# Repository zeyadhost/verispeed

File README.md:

# Verispeed

A MIDI controller with 12 keys, 2 knobs and a screen. It works with music programs on a laptop.

Verispeed is one circuit board (PCB). It has no case. The 12 keys have the layout of one piano octave: 7 white keys and 5 black keys. The screen is in the center. There is one knob on each side of the screen.

The board has no speaker, so it does not make sound. It is a MIDI device. Connect it to a laptop with a USB-C cable. A music program on the laptop makes the sound. The program can be a DAW (digital audio workstation) or a software synthesizer.

The board also has Bluetooth LE. You can use it with a phone or a tablet.

Status: The design is finished and has no errors. The board is not built yet. The firmware is not written yet.

## Features

- 12 keys (MX-style switches), with 1 diode for each key
- 2 rotary encoders with a push button
- 2 inch color screen, 240 x 320 pixels
- ESP32-S3 module with USB and Bluetooth LE (8 MB flash, 2 MB PSRAM)
- Power from USB-C or from a 1-cell LiPo battery
- Battery charger on the board (200 mA)
- BOOT button, RESET button, serial header and 5 test points
- Board size 155 mm x 99 mm, 2 layers, 4 holes for M3 screws

## How it works

- Power: USB-C gives 5 V. A diode (D1) sends the 5 V to the system rail (SYS). The regulator U4 makes 3.3 V from SYS.
- Power source: When USB is connected, the P-MOSFET Q1 disconnects the battery. When USB is not connected, Q1 connects the battery.
- Battery: The charger U3 charges the battery at 200 mA. The red LED D2 is on while the battery charges. The slide switch SW4 disconnects the battery from the board. The charger still works when SW4 is off.
- Battery level: R6 and R7 divide the battery voltage by 2. GPIO1 reads the result. Multiply the value by 2 to get the battery voltage.
- USB: U2 protects the USB data lines from static electricity. R1 and R2 tell a USB-C power source to give 5 V. The ESP32-S3 has native USB, so it can be a USB-MIDI device with no extra chip.
- Keys: The 12 keys are in a matrix of 3 rows and 4 columns. The diode of each key points from the column to the row.
- Screen: The screen connects to the header J4 and uses the default SPI pins. GPIO14 controls the backlight.
- Firmware: To load new firmware, hold the BOOT button (SW2) and push the RESET button (SW1). The ESP32-S3 then waits for new firmware on USB. The header J3 has GND, TX and RX for a serial adapter.
- Test points: TP1 is 5 V from USB. TP2 is the battery. TP3 is SYS. TP4 is 3.3 V. TP5 is GND.

## Pictures

The picture shows the wires of the PCB. Red wires are on the top side. Blue wires are on the bottom side. The picture does not show the ground fill.

The flag and the signature are on the silkscreen (the white print on the board). Their SVG files are in [pcb-v2/silkscreen-art](pcb-v2/silkscreen-art/).

## Parts

The full build costs about $75. The prices are from 2 November 2026 and do not include shipping. Check the stock and the part numbers again before you order.

The LCSC parts cost about $24, the screen about $11, the battery about $10 and the PCB about $12. The switches, keycaps, knobs and screws cost the rest.

| Qty | Part | Reference | Where to buy |
|---|---|---|---|
| 1 | ESP32-S3-WROOM-1-N8R2 module | U5 | LCSC C2913204 |
| 1 | MCP73831-2-OT battery charger | U3 | LCSC C14879 |
| 1 | AP2112K-3.3 regulator | U4 | LCSC C51118 |
| 1 | USBLC6-2SC6 USB protection | U2 | LCSC C7519 |
| 1 | AO3401A P-MOSFET | Q1 | LCSC C15127 |
| 12 | 1N4148W diode | D3 to D14 | LCSC C81598 |
| 1 | SS14 Schottky diode | D1 | LCSC C2480 |
| 1 | KT-0603R red LED | D2 | LCSC C2286 |
| 1 | GCT USB4085 USB-C socket | J1 | LCSC C7095263 |
| 1 | JST B2B-PH-K-S battery socket | J2 | LCSC C131337 |
| 1 | 1 x 3 pin header, 2.54 mm | J3 | LCSC C49257 |
| 1 | 1 x 8 pin header, 2.54 mm, long pins | J4 | LCSC C492407 |
| 2 | Omron B3F-1000 push button | SW1 (RESET), SW2 (BOOT) | LCSC C93157 |
| 1 | G-Switch SK-12D02-G050 slide switch | SW4 | LCSC C5211273 |
| 2 | Alps EC11E15244G1 rotary encoder | ENC1, ENC2 | LCSC C370970 |
| 2 | 100 nF capacitor, 0603 | C5, C6 | LCSC C1591 |
| 2 | 1 uF capacitor, 0603 | C3, C7 | LCSC C15849 |
| 2 | 4.7 uF capacitor, 0805 | C1, C2 | LCSC C1779 |
| 1 | 10 uF capacitor, 0805 | C4 | LCSC C15850 |
| 1 | 1 kOhm resistor, 0603 | R5 | LCSC C21190 |
| 1 | 4.99 kOhm resistor, 0603 (the schematic says 5 kOhm) | R4 | LCSC C23046 |
| 2 | 5.1 kOhm resistor, 0603 | R1, R2 | LCSC C23186 |
| 2 | 10 kOhm resistor, 0603 | R8, R9 | LCSC C25804 |
| 3 | 100 kOhm resistor, 0603 | R3, R6, R7 | LCSC C25803 |
| 1 | Waveshare 2 inch LCD module (SKU 17344) | J4 | Waveshare |
| 1 | LiPo battery, 3.7 V, 1200 mAh, JST-PH plug (Adafruit 258) | J2 | Adafruit |
| 12 | MX-style switch, 5 pin, PCB mount | K1 to K12 | Keyboard shop |
| 12 | Keycap, 1u | K1 to K12 | Keyboard shop |
| 2 | Knob for a 6 mm flat (D-cut) shaft | ENC1, ENC2 | Any shop |
| 4 | M3 standoff, female-female, 12 mm or longer | H1 to H4 | Any shop |
| 4 | M3 x 6 screw | H1 to H4 | Any shop |
| 4 | M2 x 6 stud and screw for the screen | J4 | Any shop |

Warning: On J2, pin 1 is plus and pin 2 is minus. Some batteries have the wires in the opposite order. Use a multimeter to check the plug before you connect the battery.

## Pin map

| Function | ESP32-S3 GPIO |
|---|---|
| Key rows ROW1, ROW2, ROW3 | 4, 5, 6 |
| Key columns COL1, COL2, COL3, COL4 | 7, 15, 16, 17 |
| Encoder 1: A, B, button | 18, 21, 38 |
| Encoder 2: A, B, button | 47, 48, 2 |
| Screen: MOSI, SCK, CS, DC, RST, backlight | 11, 12, 10, 9, 8, 14 |
| Battery level (half of the battery voltage) | 1 |
| USB D-, D+ | 19, 20 |
| Serial header J3: TX, RX | 43, 44 |
| BOOT button | 0 |
| RESET button | EN |

## Key matrix

Each key connects a column to a diode. The diode connects to the row.

| Key | Row | Column | Position |
|---|---|---|---|
| K1 | ROW1 | COL1 | 1st white key (left) |
| K5 | ROW2 | COL1 | 2nd white key |
| K2 | ROW1 | COL2 | 3rd white key |
| K6 | ROW2 | COL2 | 4th white key |
| K3 | ROW1 | COL3 | 5th white key |
| K7 | ROW2 | COL3 | 6th white key |
| K4 | ROW1 | COL4 | 7th white key (right) |
| K9 | ROW3 | COL1 | 1st black key (left) |
| K10 | ROW3 | COL2 | 2nd black key |
| K11 | ROW3 | COL3 | 3rd black key |
| K12 | ROW3 | COL4 | 4th black key |
| K8 | ROW2 | COL4 | 5th black key (right) |

## Open the design

Open `pcb-v2/audio.kicad_pro` in KiCad 10. Keep the files and folders of `pcb-v2` together.

To run the checks from the command line:

```bash
cd pcb-v2
kicad-cli sch erc audio.kicad_sch
kicad-cli pcb drc --refill-zones --schematic-parity audio.kicad_pcb
```

ERC shows 0 violations. DRC shows 0 errors, 0 unconnected items and 0 differences from the schematic. DRC also shows 21 warnings. All 21 warnings are about the silkscreen.

## Files

```
pcb-v2/
  audio.kicad_pro       project file (open this file)
  audio.kicad_sch       schematic
  audio.kicad_pcb       PCB layout
  fp-lib-table          list of footprint libraries
  verispeed-v2.pretty/  custom footprints
  3dmodels/             3D models of the encoder and the screen
  silkscreen-art/       SVG files of the flag and the signature
images/                 pictures for this page and the journal
JOURNAL.md              development log
```

## Credits

- The Hack Club flag is from [assets.hackclub.com](https://assets.hackclub.com/).
- The 3D models of the Alps encoder and the Waveshare screen are from the makers. The other 3D models are from the KiCad library.

## License

MIT License. See [LICENSE](LICENSE).

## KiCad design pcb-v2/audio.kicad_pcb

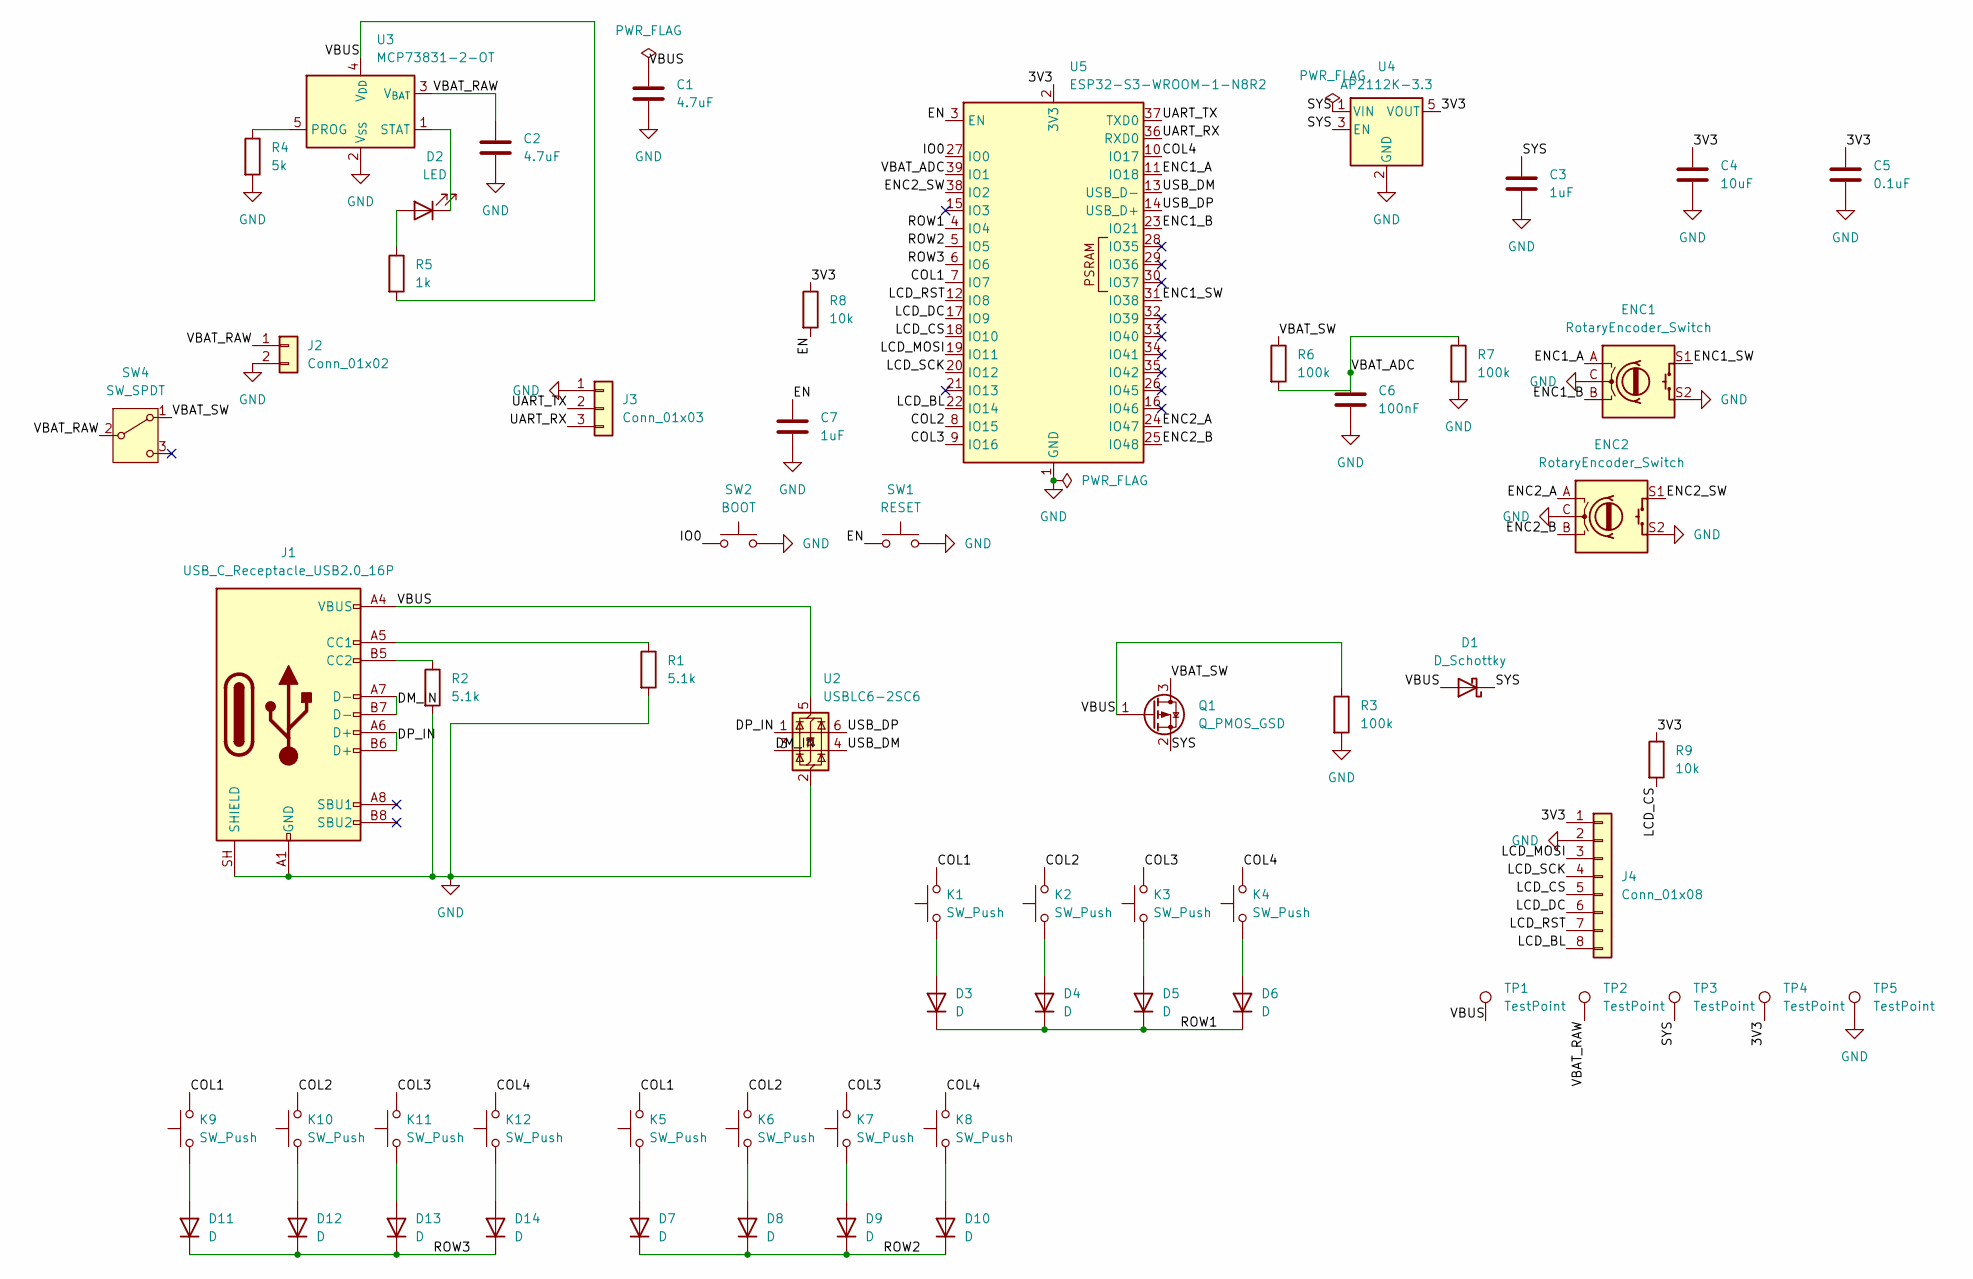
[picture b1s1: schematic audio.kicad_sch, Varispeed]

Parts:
C1, C2: 4.7uF; C_0805_2012Metric_Pad1.18x1.45mm_HandSolder
C3, C7: 1uF; C_0603_1608Metric_Pad1.08x0.95mm_HandSolder
C4: 10uF; C_0805_2012Metric_Pad1.18x1.45mm_HandSolder
C5: 0.1uF; C_0603_1608Metric_Pad1.08x0.95mm_HandSolder
C6: 100nF; C_0603_1608Metric_Pad1.08x0.95mm_HandSolder
D1: D_Schottky; D_SMA
D2: LED; LED_0603_1608Metric_Pad1.05x0.95mm_HandSolder
D3, D4, D5, D6, D7, D8, D9, D10, D11, D12, D13, D14: D; D_SOD-123
ENC1, ENC2: RotaryEncoder_Switch; RotaryEncoder_Alps_EC11E15244G1_Vertical
J1: USB_C_Receptacle_USB2.0_16P; USB_C_Receptacle_GCT_USB4085_FinePitch
J2: Conn_01x02; JST_PH_B2B-PH-K_1x02_P2.00mm_Vertical
J3: Conn_01x03; PinHeader_1x03_P2.54mm_Vertical
J4: Conn_01x08; Waveshare_2inch_LCD_Module
K1, K2, K3, K4, K5, K6, K7, K8, K9, K10, K11, K12: SW_Push; SW_Cherry_MX_1.00u_PCB
Q1: Q_PMOS_GSD; SOT-23
R1, R2: 5.1k; R_0603_1608Metric_Pad0.98x0.95mm_HandSolder
R3, R6, R7: 100k; R_0603_1608Metric_Pad0.98x0.95mm_HandSolder
R4: 5k; R_0603_1608Metric_Pad0.98x0.95mm_HandSolder
R5: 1k; R_0603_1608Metric_Pad0.98x0.95mm_HandSolder
R8, R9: 10k; R_0603_1608Metric_Pad0.98x0.95mm_HandSolder
SW1: RESET; SW_TH_Tactile_Omron_B3F-100x
SW2: BOOT; SW_TH_Tactile_Omron_B3F-100x
SW4: SW_SPDT; SW_Slide_SPDT_Angled_GSwitch_SK-12D02
TP1, TP2, TP3, TP4, TP5: TestPoint; TestPoint_Pad_D2.0mm
U2: USBLC6-2SC6; SOT-23-6
U3: MCP73831-2-OT; SOT-23-5
U4: AP2112K-3.3; SOT-23-5
U5: ESP32-S3-WROOM-1-N8R2; ESP32-S3-WROOM-1_Via0.3mm

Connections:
/3V3: C4.1, C5.1, J4.1, R8.1, R9.1, TP4.1 (1_1), U4.5 (VOUT), U5.2 (3V3)
/COL1: K1.2, K5.2, K9.2, U5.7 (IO7)
/COL2: K2.2, K6.2, K10.2, U5.8 (IO15)
/COL3: K3.2, K7.2, K11.2, U5.9 (IO16)
/COL4: K4.2, K8.2, K12.2, U5.10 (IO17)
/DM_IN: J1.A7 (D-), J1.B7 (D-), U2.3 (I/O2)
/DP_IN: J1.A6 (D+), J1.B6 (D+), U2.1 (I/O1)
/EN: C7.1, R8.2, SW1.1, U5.3 (EN)
/ENC1_A: ENC1.A, U5.11 (IO18)
/ENC1_B: ENC1.B, U5.23 (IO21)
/ENC1_SW: ENC1.S1, U5.31 (IO38)
/ENC2_A: ENC2.A, U5.24 (IO47)
/ENC2_B: ENC2.B, U5.25 (IO48)
/ENC2_SW: ENC2.S1, U5.38 (IO2)
/IO0: SW2.1, U5.27 (IO0)
/LCD_BL: J4.8, U5.22 (IO14)
/LCD_CS: J4.5, R9.2, U5.18 (IO10)
/LCD_DC: J4.6, U5.17 (IO9)
/LCD_MOSI: J4.3, U5.19 (IO11)
/LCD_RST: J4.7, U5.12 (IO8)
/LCD_SCK: J4.4, U5.20 (IO12)
/ROW1: D3.1 (K), D4.1 (K), D5.1 (K), D6.1 (K), U5.4 (IO4)
/ROW2: D7.1 (K), D8.1 (K), D9.1 (K), D10.1 (K), U5.5 (IO5)
/ROW3: D11.1 (K), D12.1 (K), D13.1 (K), D14.1 (K), U5.6 (IO6)
/SYS: C3.1, D1.1 (K), Q1.2 (S), TP3.1 (1_1), U4.1 (VIN), U4.3 (EN)
/UART_RX: J3.3, U5.36 (RXD0)
/UART_TX: J3.2, U5.37 (TXD0)
/USB_DM: U2.4 (I/O2), U5.13 (USB_D-)
/USB_DP: U2.6 (I/O1), U5.14 (USB_D+)
/VBAT_ADC: C6.1, R6.2, R7.1, U5.39 (IO1)
/VBAT_RAW: C2.1, J2.1, SW4.2 (B), TP2.1 (1_1), U3.3 (V_{BAT})
/VBAT_SW: Q1.3 (D), R6.1, SW4.1 (A)
/VBUS: C1.1, D1.2 (A), J1.A4 (VBUS), J1.A9 (VBUS), J1.B4 (VBUS), J1.B9 (VBUS), Q1.1 (G), R3.1, R5.2, TP1.1 (1_1), U2.5 (VBUS), U3.4 (V_{DD})
GND: C1.2, C2.2, C3.2, C4.2, C5.2, C6.2, C7.2, ENC1.C, ENC1.S2, ENC2.C, ENC2.S2, J1.A1 (GND), J1.A12 (GND), J1.B1 (GND), J1.B12 (GND), J1.SH (SHIELD), J2.2, J3.1, J4.2, R1.2, R2.2, R3.2, R4.2, R7.2, SW1.2, SW2.2, TP5.1 (1_1), U2.2 (GND), U3.2 (V_{SS}), U4.2 (GND), U5.1 (GND), U5.40 (GND), U5.41 (GND)
unnamed: D2.2 (A), R5.1
unnamed: D2.1 (K), U3.1 (STAT)
unnamed: D3.2 (A), K1.1
unnamed: D4.2 (A), K2.1
unnamed: D5.2 (A), K3.1
unnamed: D6.2 (A), K4.1
unnamed: D7.2 (A), K5.1
unnamed: D8.2 (A), K6.1
unnamed: D9.2 (A), K7.1
unnamed: D10.2 (A), K8.1
unnamed: D11.2 (A), K9.1
unnamed: D12.2 (A), K10.1
unnamed: D13.2 (A), K11.1
unnamed: D14.2 (A), K12.1
unnamed: J1.A5 (CC1), R1.1
unnamed: J1.B5 (CC2), R2.1
unnamed: R4.1, U3.5 (PROG)

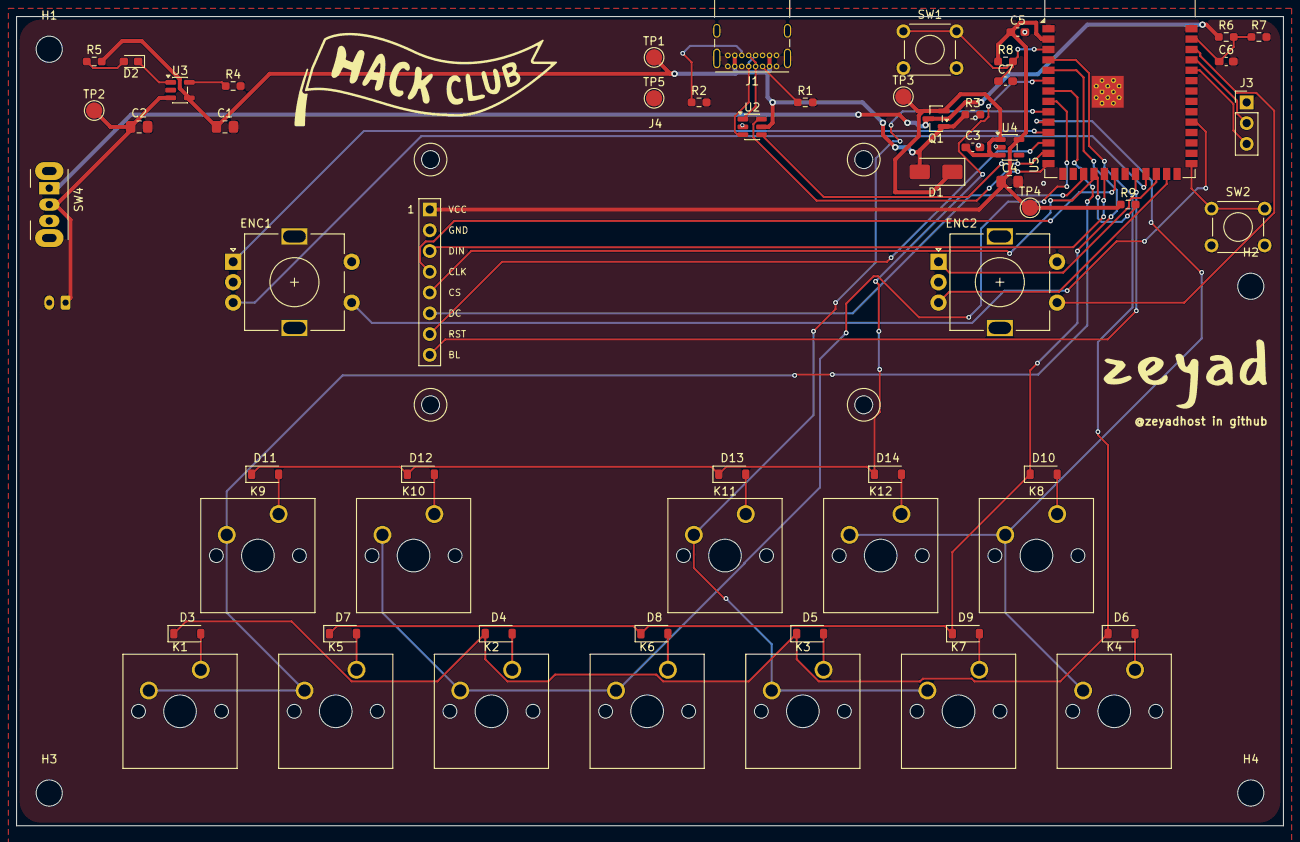
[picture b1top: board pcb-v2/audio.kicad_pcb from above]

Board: 2 copper layers, 155.0 x 99.0 mm, 65 parts (1 on the bottom side), 51 nets.

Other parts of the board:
H1, H2, H3, H4: MountingHole_3.2mm_M3

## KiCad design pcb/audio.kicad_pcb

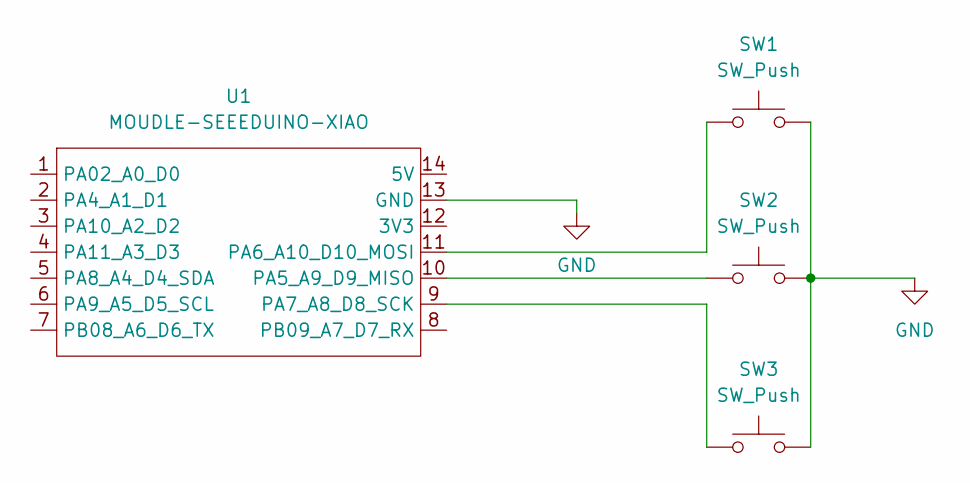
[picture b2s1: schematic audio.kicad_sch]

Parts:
SW1, SW2, SW3: SW_Push; SW_Cherry_MX_1.00u_PCB
U1: MOUDLE-SEEEDUINO-XIAO; XIAO-Generic-Hybrid-14P-2.54-21X17.8MM

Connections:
GND: SW1.2, SW2.2, SW3.2, U1.13 (GND)
unnamed: SW2.1, U1.10 (PA5_A9_D9_MISO)
unnamed: SW1.1, U1.11 (PA6_A10_D10_MOSI)
unnamed: SW3.1, U1.9 (PA7_A8_D8_SCK)

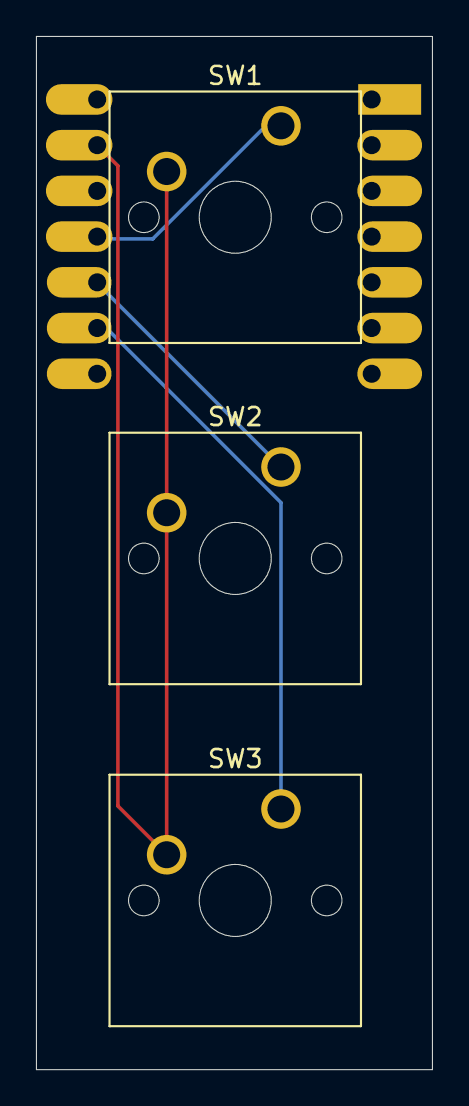
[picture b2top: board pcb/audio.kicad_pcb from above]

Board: 2 copper layers, 22.0 x 57.4 mm, 4 parts (1 on the bottom side), 4 nets.
